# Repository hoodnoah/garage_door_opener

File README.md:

# ESP32 Rust Development Environment

A Nix-based development environment for ESP32 Rust projects. Uses the official [esp-rs/esp-idf-template](https://github.com/esp-rs/esp-idf-template) for project generation, ensuring version compatibility is maintained by the esp-rs team.

## Quick Start

```bash
nix develop                  # Enter development shell
just init my_project         # Generate Rust project (interactive)
just setup                   # Install ESP toolchain (one-time)
# Restart shell to pick up toolchain
just build                   # Compile
just flash                   # Flash to device and monitor
```

## What This Template Provides

This template provides the development environment and conveniences:

| File | Purpose |
|------|---------|
| `flake.nix` | Nix dev shell with system dependencies |
| `.envrc` | Direnv integration for auto-loading |
| `justfile` | Convenience commands |
| `partitions.csv` | Flash partition layout |
| `.env.example` | Template for WiFi/MQTT secrets |

The actual Rust project files (`Cargo.toml`, `src/`, `.cargo/`, etc.) are generated by running `just init`, which uses the official esp-rs template. This ensures dependency versions stay compatible with ESP-IDF.

## Commands

| Command | Description |
|---------|-------------|
| `just init <name>` | Generate Rust project using esp-rs template |
| `just setup` | Install ESP toolchain |
| `just build` | Debug build |
| `just build-release` | Release build (size-optimized) |
| `just flash` | Flash and monitor |
| `just flash-only` | Flash without monitor |
| `just monitor` | Serial monitor only |
| `just clean` | Remove build artifacts |
| `just clean-all` | Remove build artifacts and ESP-IDF cache |
| `just size` | Show binary size breakdown |

## Configuration

### Target Selection

When running `just init`, you'll be prompted to select your target chip (ESP32, ESP32-S3, ESP32-C3, etc.). The template handles the configuration automatically.

### Environment Variables

Copy `.env.example` to `.env` for compile-time configuration (WiFi credentials, etc.):

```bash
cp .env.example .env
```

### Flash Partitions

`partitions.csv` defines the flash layout. Adjust sizes based on your needs and flash size.

## Using as a GitHub Template

1. On GitHub, go to repository **Settings** > **General**
2. Check **Template repository**

Then create new projects via:
- GitHub UI: Click **Use this template**
- CLI: `gh repo create my-project --template USERNAME/esp32_template --clone`

After creating, run `just init <name>` to generate the Rust project.

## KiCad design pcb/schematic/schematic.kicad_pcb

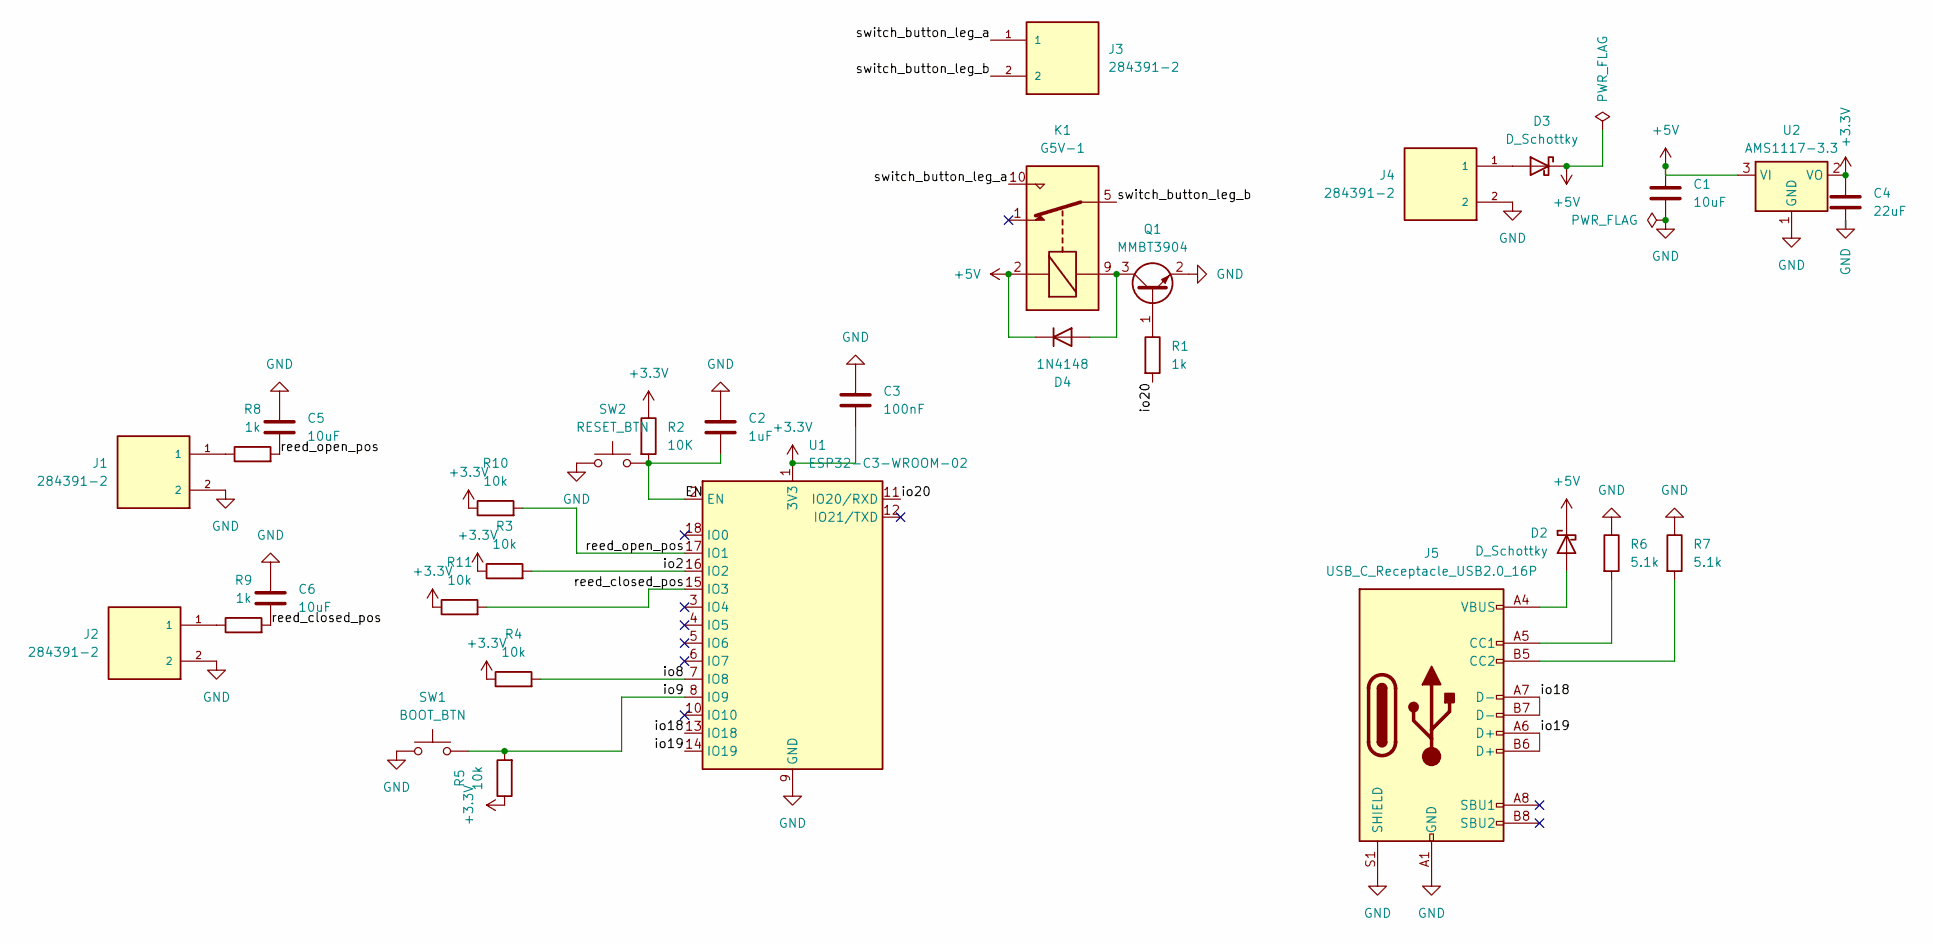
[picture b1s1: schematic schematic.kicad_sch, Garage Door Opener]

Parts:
C1, C5, C6: 10uF; C_0805_2012Metric; LCSC Part # C440198
C2: 1uF; C_0805_2012Metric; LCSC Part # C28323
C3: 100nF; C_0805_2012Metric; LCSC Part # C49678
C4: 22uF; C_0805_2012Metric; LCSC Part # C45783
D2, D3: D_Schottky; D_SOD-123; LCSC Part # C8598
D4: 1N4148; D_SOD-123; LCSC Part # C81598
J1, J2, J3, J4: 284391-2; TE_284391-2; PARTREV C; jlcpcb_part_no C3820579
J5: USB_C_Receptacle_USB2.0_16P; USB_C_Receptacle_HRO_TYPE-C-31-M-12; LCSC Part # C165948
K1: G5V-1; Relay_SPDT_Omron_G5V-1
Q1: MMBT3904; SOT-23; LCSC Part # C2145
R1, R8, R9: 1k; R_0805_2012Metric; LCSC Part # C17513
R2: 10K; R_0805_2012Metric; LCSC Part # C17414
R3, R4, R5, R10, R11: 10k; R_0805_2012Metric; LCSC Part # C17414
R6, R7: 5.1k; R_0805_2012Metric; LCSC Part # C27834
SW1: BOOT_BTN; SW_SPST_TS-1088-xR025; LCSC Part # C720477
SW2: RESET_BTN; SW_SPST_TS-1088-xR025; LCSC Part # C720477
U1: ESP32-C3-WROOM-02; LCSC Part # C2934560
U2: AMS1117-3.3; SOT-223-3_TabPin2; LCSC Part # C6186

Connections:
+3.3V: C3.2, C4.1, R2.1, R3.1, R4.1, R5.1, R10.1, R11.1, U1.1 (3V3), U2.2 (VO)
+5V: C1.1, D2.1 (K), D3.1 (K), D4.1 (K), K1.2, U2.3 (VI)
/EN: C2.2, R2.2, SW2.2, U1.2 (EN)
/io2: R3.2, U1.16 (IO2)
/io8: R4.2, U1.7 (IO8)
/io9: R5.2, SW1.2, U1.8 (IO9)
/io18: J5.A7 (D-), J5.B7 (D-), U1.13 (IO18)
/io19: J5.A6 (D+), J5.B6 (D+), U1.14 (IO19)
/io20: R1.2, U1.11 (IO20/RXD)
/reed_closed_pos: C6.2, R9.2, R11.2, U1.15 (IO3)
/reed_open_pos: C5.2, R8.2, R10.2, U1.17 (IO1)
/switch_button_leg_a: J3.1, K1.10
/switch_button_leg_b: J3.2, K1.5, K1.6
GND: C1.2, C2.1, C3.1, C4.2, C5.1, C6.1, J1.2, J2.2, J4.2, J5.A1 (GND), J5.A12 (GND), J5.B1 (GND), J5.B12 (GND), J5.S1 (SHIELD), Q1.2 (E), R6.1, R7.1, SW1.1, SW2.1, U1.9 (GND), U1.19 (GND), U2.1 (GND)
unnamed: D2.2 (A), J5.A4 (VBUS), J5.A9 (VBUS), J5.B4 (VBUS), J5.B9 (VBUS)
unnamed: D3.2 (A), J4.1
unnamed: D4.2 (A), K1.9, Q1.3 (C)
unnamed: J1.1, R8.1
unnamed: J2.1, R9.1
unnamed: J5.A5 (CC1), R6.2
unnamed: J5.B5 (CC2), R7.2
unnamed: Q1.1 (B), R1.1

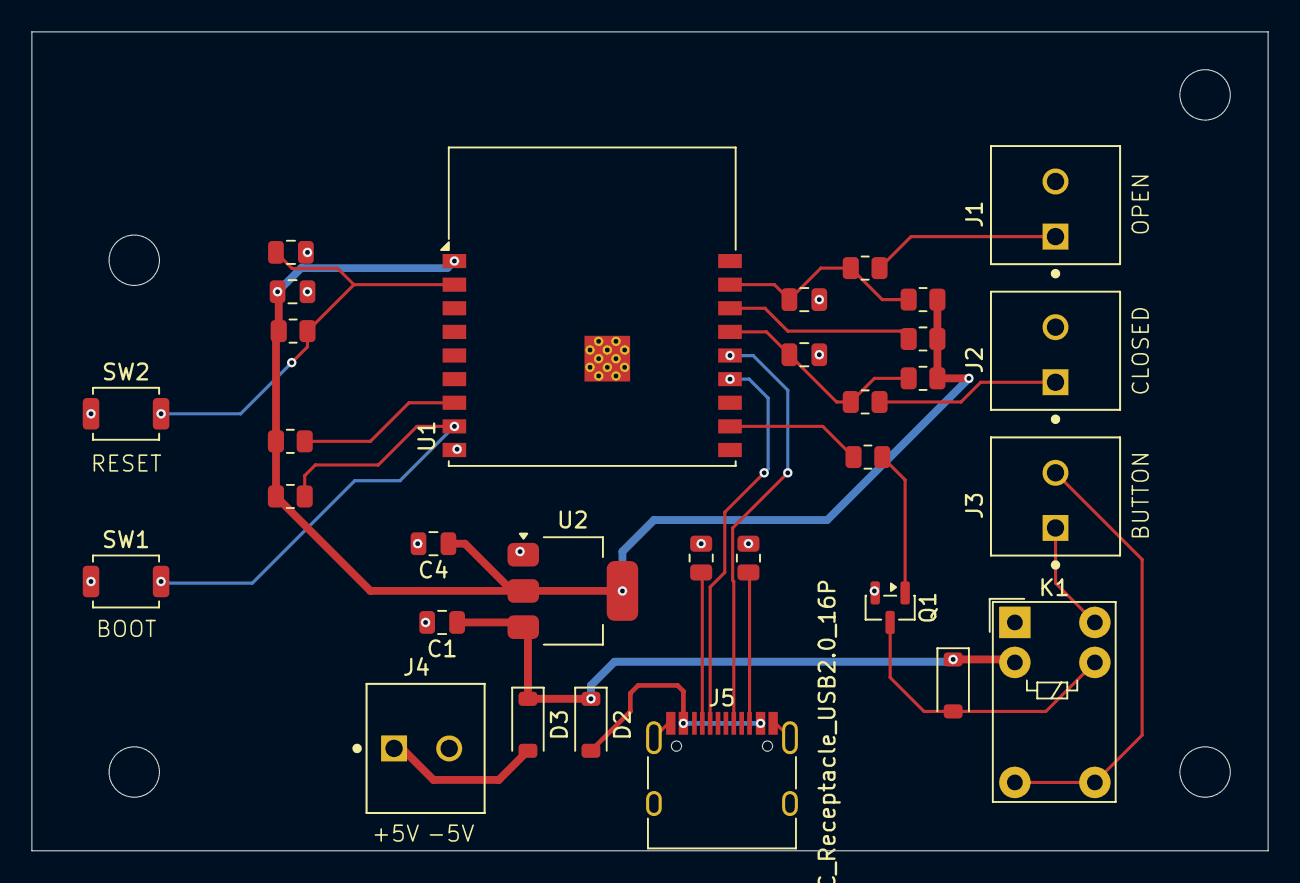
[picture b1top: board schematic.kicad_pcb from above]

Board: 2 copper layers, 78.5 x 52.0 mm, 31 parts (0 on the bottom side), 22 nets.

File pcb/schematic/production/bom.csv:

Designator,Footprint,Quantity,Value,LCSC Part #
"C1, C5, C6",0805,3,10uF,C440198
C2,0805,1,1uF,C28323
C3,0805,1,100nF,C49678
C4,CP_EIA-3216-18_Kemet-A_HandSolder,1,22uF Tantalum,C45783
"D2, D3",D_SOD-123,2,D_Schottky,C8598
D4,D_SOD-123,1,1N4148,C81598
J5,USB_C_Receptacle_HRO_TYPE-C-31-M-12,1,USB_C_Receptacle_USB2.0_16P,C165948
Q1,SOT-23,1,MMBT3904,C2145
"R1, R8, R9",0805,3,1k,C17513
"R10, R11, R2, R3, R4, R5",0805,6,10k,C17414
"R6, R7",0805,2,5.1k,C27834
SW1,SW_SPST_TS-1088-xR025,1,BOOT_BTN,C720477
SW2,SW_SPST_TS-1088-xR025,1,RESET_BTN,C720477
U1,ESP32-C3-WROOM-02,1,ESP32-C3-WROOM-02,C2934560
U2,SOT-223-3_TabPin2,1,AMS1117-3.3,C6186

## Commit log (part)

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2026-01-18 new, empty, tested project
2026-01-18 implement, test garage door state machine
2026-01-18 fix state change boolean return to be true when changed, false when same
2026-01-18 reduce test verbosity with helper fn
2026-01-23 finalize state machine implementation, implement reed_switch, relay, garage_door_controller abstractions, retrofit mqtt/wifi libs
2026-01-23 add command reception to mqtt
2026-01-23 alter endpoints to permit use of more than one garage door opener
2026-02-24 import display
2026-02-24 abandon nix
2026-02-25 working first version
2026-02-25 add can_close, can_open methods to state machine
2026-02-25 move open/close logic into garage door controller, open/close availability into state machine
2026-02-25 fully tested on breadboard, ready for prototype on actual unit
2026-02-28 PCB v1
2026-02-28 gitignore zips
2026-02-28 add home-assistant card for opener
2026-03-02 update footprint of C4 capacitor to 0805
2026-03-05 update debounce logic to ensure state is stable for the full debounce window before accepting a change
2026-03-05 update debounce delay to 500ms (500,000us)
2026-03-13 update pin assignments, fix silkscreen on boot, reset buttons
2026-03-13 fix silkscreen for boot, reset buttons
2026-04-09 pcb updates
2026-04-09 fix: if the mcu came up before Home-Assistant and timed out (e.g. during power outage), main loop would return on error
2026-04-09 update reed switch to remove fields which are set but never read
2026-04-09 remove illusory states from reed switch; read initial value and set to that on creation
2026-04-09 simplify generic types w/ esp_idf_hal's AnyIOPin
2026-04-09 fix minor error in main
2026-06-06 add reboot signal for long-term-lost mqtt connection
2026-06-06 add handler for connections
2026-06-06 fold new connections_handler into main.rs
2026-06-06 clean up niggling bugs
2026-06-07 bump Cargo version number
2026-06-07 Disconnect fix (#1)
    * add reboot signal for long-term-lost mqtt connection
    * add handler for connections
    * fold new connections_handler into main.rs
    * clean up niggling bugs
    * bump Cargo version number
2026-06-09 Add renovate.json
2026-06-09 Add renovate.json (#2)
